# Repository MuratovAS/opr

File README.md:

# OPR
Open pocket router

## Screenshots

## In developing!!!

If you have questions, write suggestions in `Issues`

## Description
TODO:

## Specification

- CPU: MT7621A
- RAM: 2Gbit DDR3 
- USB: 3.0
- ETH: 3xGbE (RJ45)
- Display: SSD1306-0.91
- Flash: W25Q256FVEIG
- PowerBank: IP5328P
- Connectors: M.2 (2xPCIe+UART); mPCIe (1xPCIe+I2C+USB2+UART)
- PCB: 6 layers; JLC06161H-3313; Epoxy Filled & Capped; 0.15mm/0.3mm Via 

## Supported modules

- WIFI: MT7612E/MT7603E (x2 mPCIe)

## Changelog:

### v 0.1
- init

## Credit
```
https://github.com/kellertk/pwnagotchi-plugin-pisugar2
https://github.com/YC-Lammy/IP5328P-powerbank_design
https://github.com/zhaoxinyu0113/MT7621A_Router_HW_DIY'
https://github.com/cyijun/MT7621A-Router-Design
https://www.cnx-software.com/2015/05/14/firewrt-is-an-openwrt-802-11ac-board-powered-by-mediatek-mt7621a-processor/
https://bbs.t-firefly.com/forum.php?mod=viewthread&tid=543
http://en.techinfodepot.shoutwiki.com/wiki/Firefly_FireWRT
https://wikidevi.wi-cat.ru/MediaTek
https://whycan.com/t_2230.html
http://bbs.ntpcb.com/read-htm-tid-44619.html
https://www.elecfans.com/soft/21/2020/202003111179546.html
```

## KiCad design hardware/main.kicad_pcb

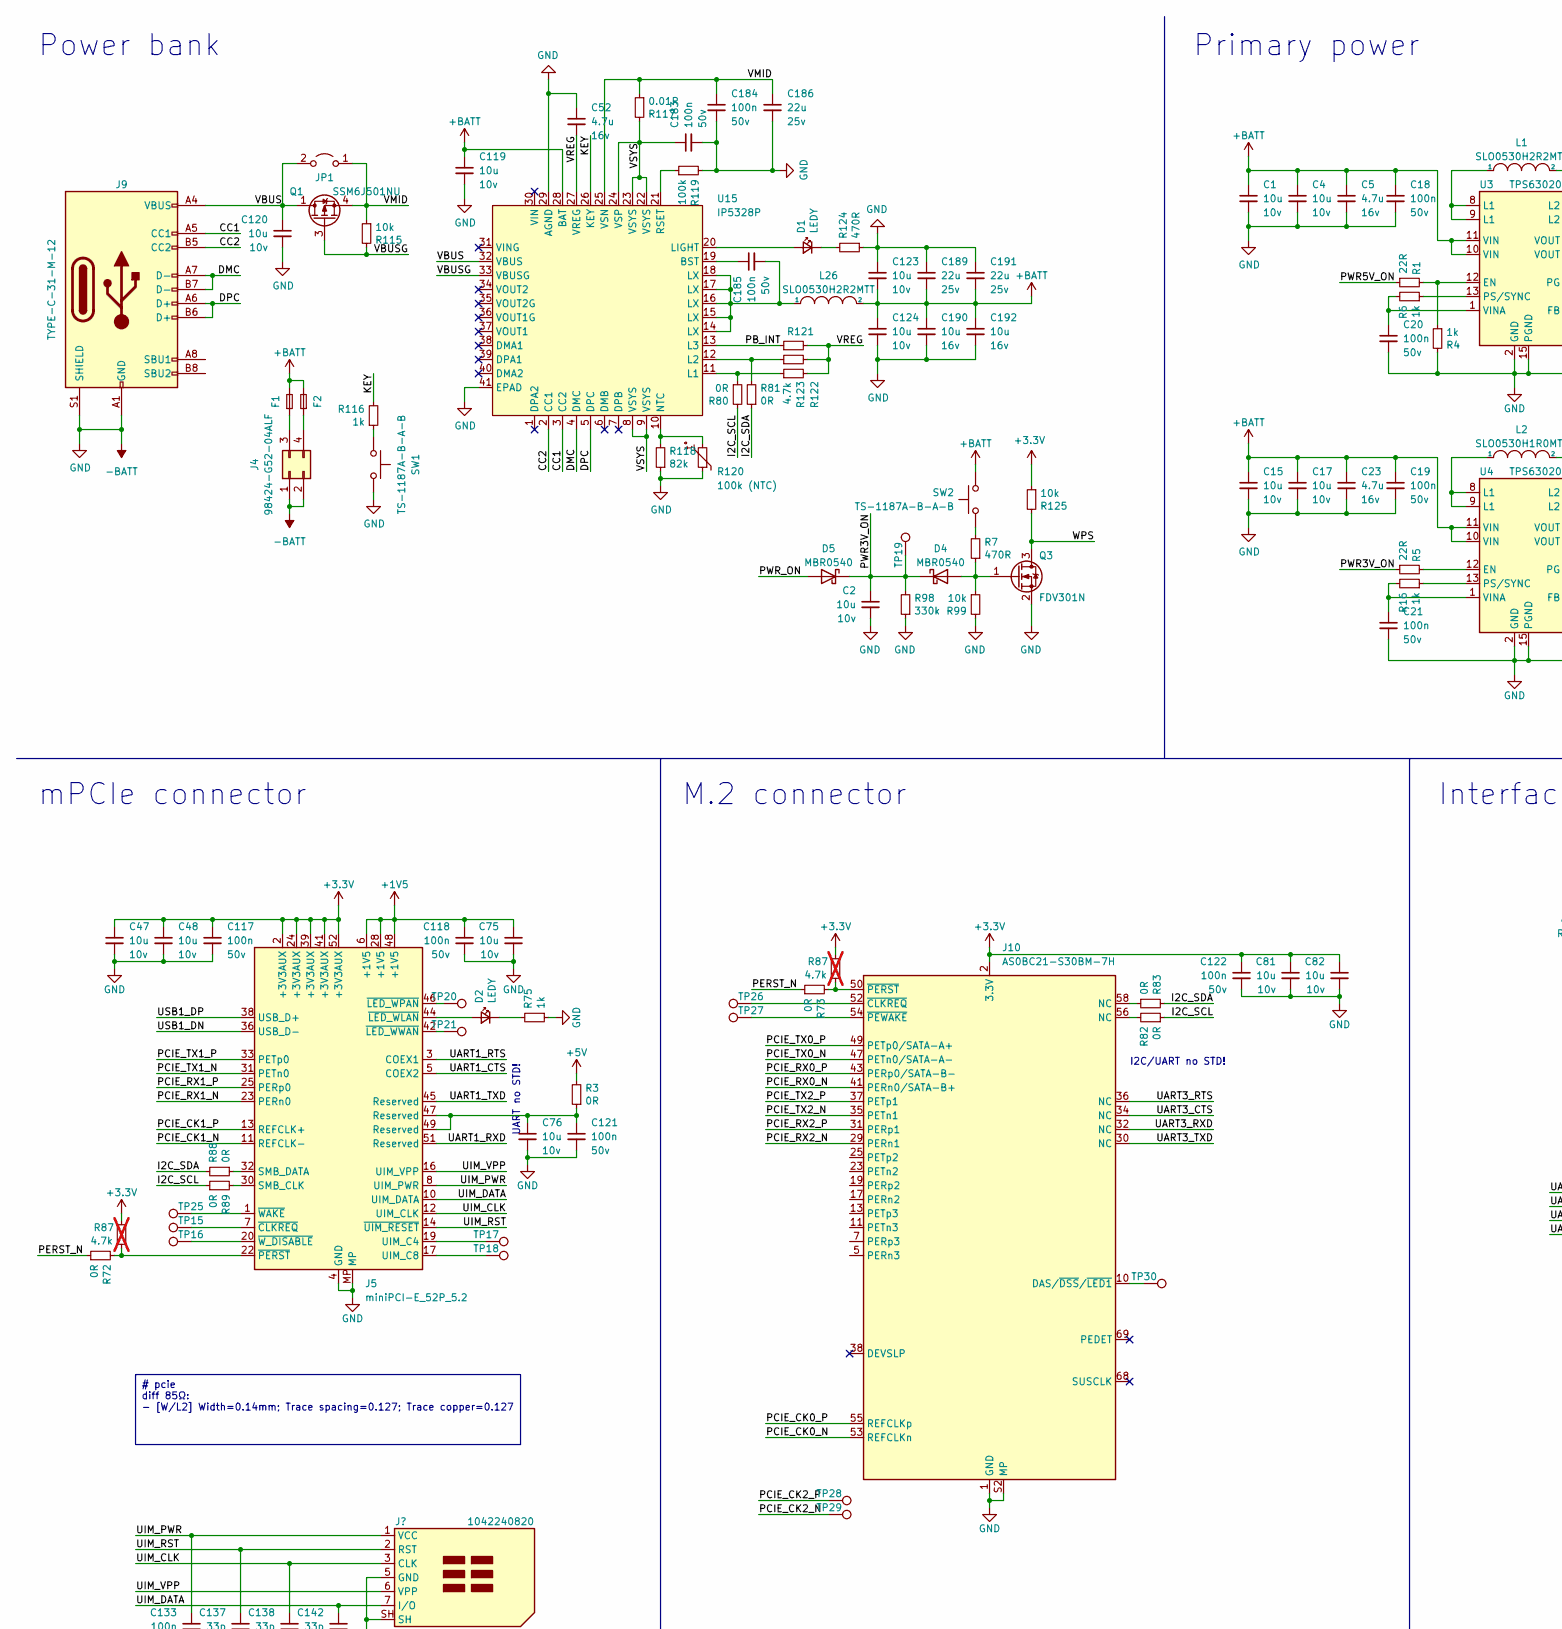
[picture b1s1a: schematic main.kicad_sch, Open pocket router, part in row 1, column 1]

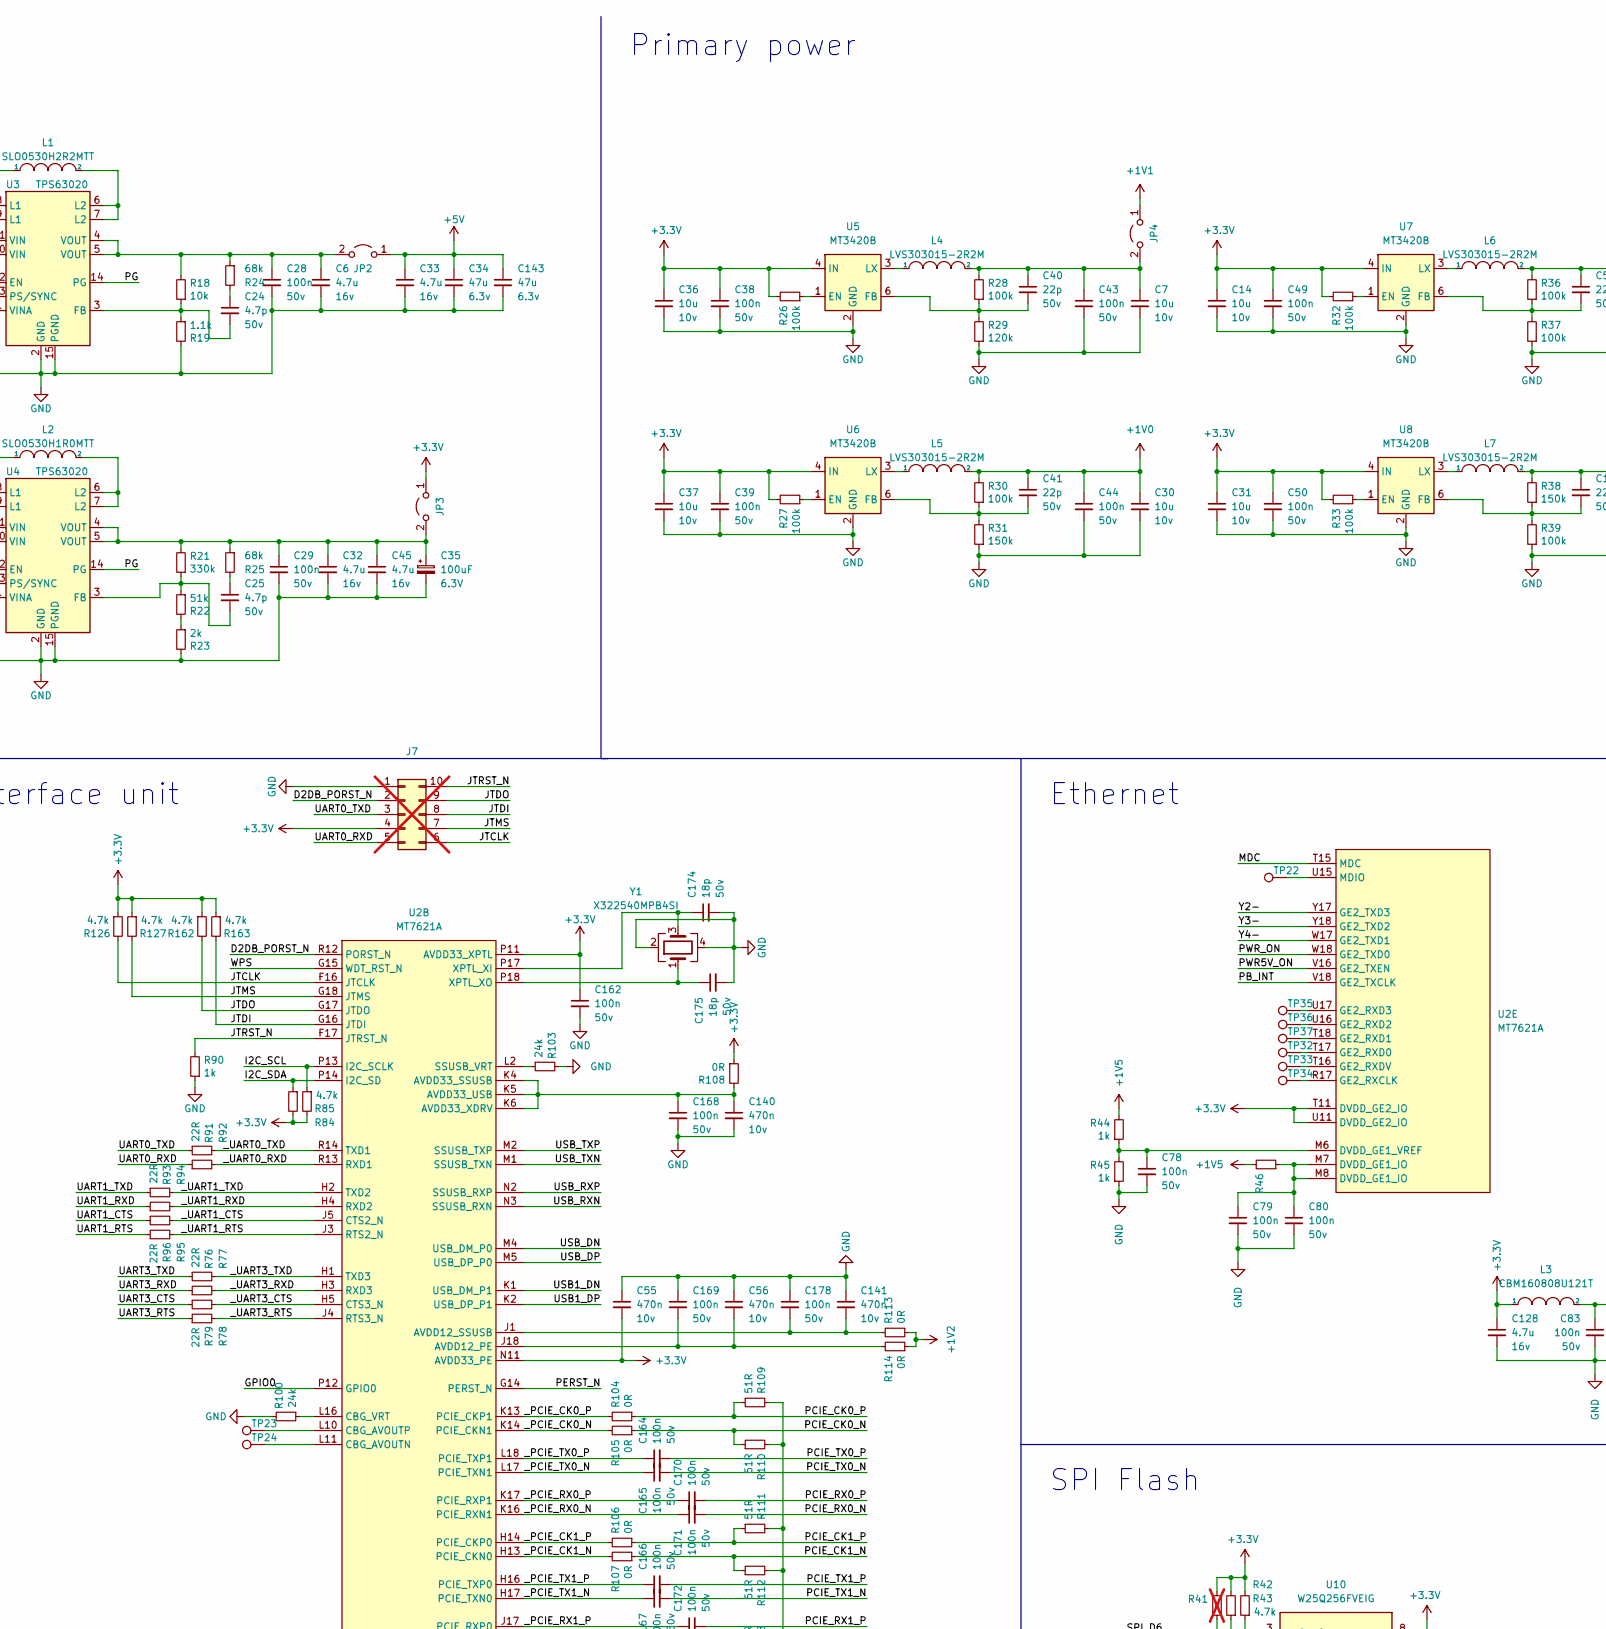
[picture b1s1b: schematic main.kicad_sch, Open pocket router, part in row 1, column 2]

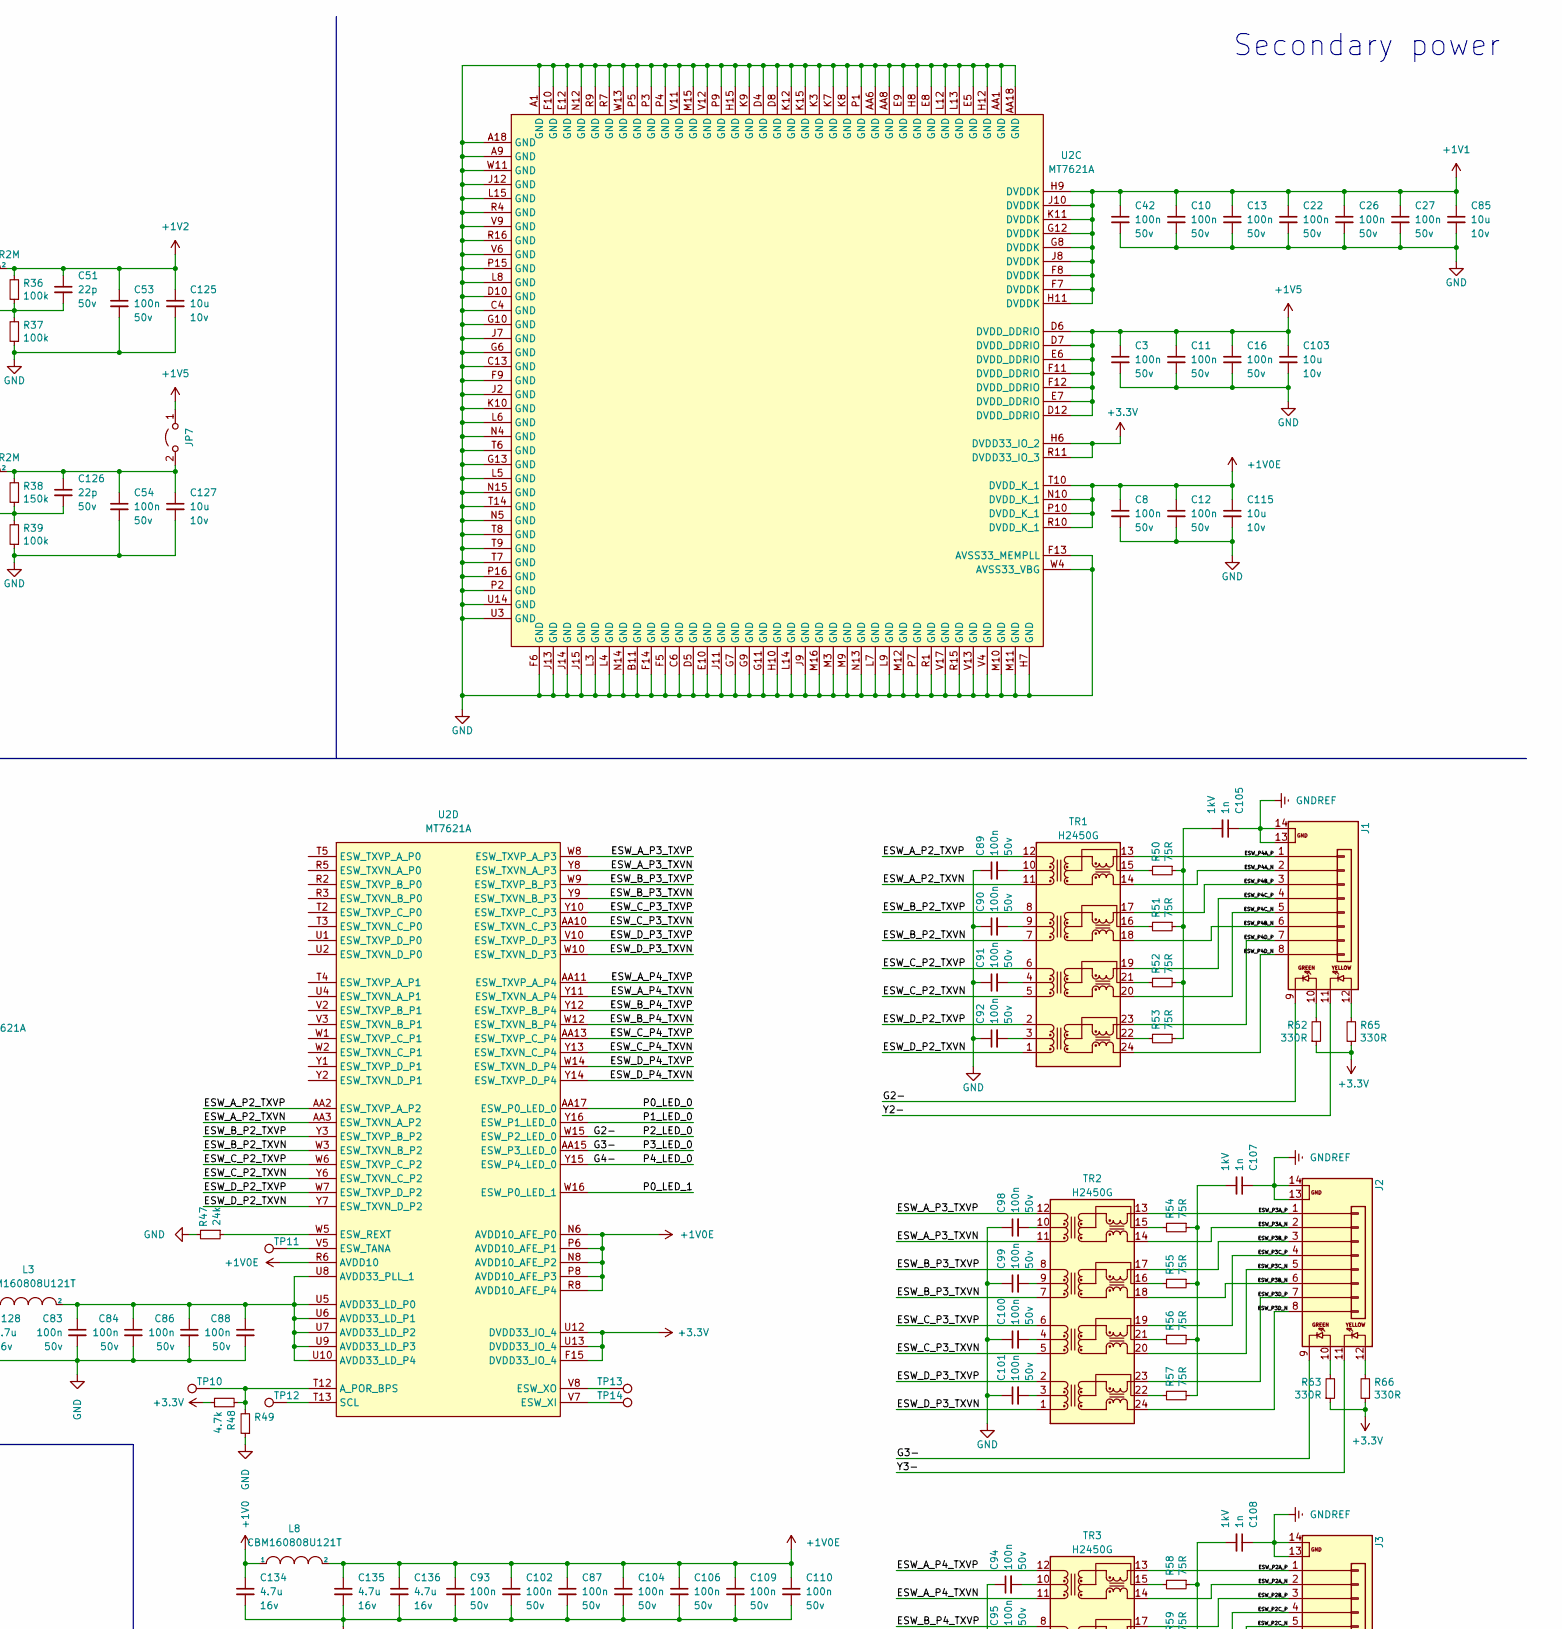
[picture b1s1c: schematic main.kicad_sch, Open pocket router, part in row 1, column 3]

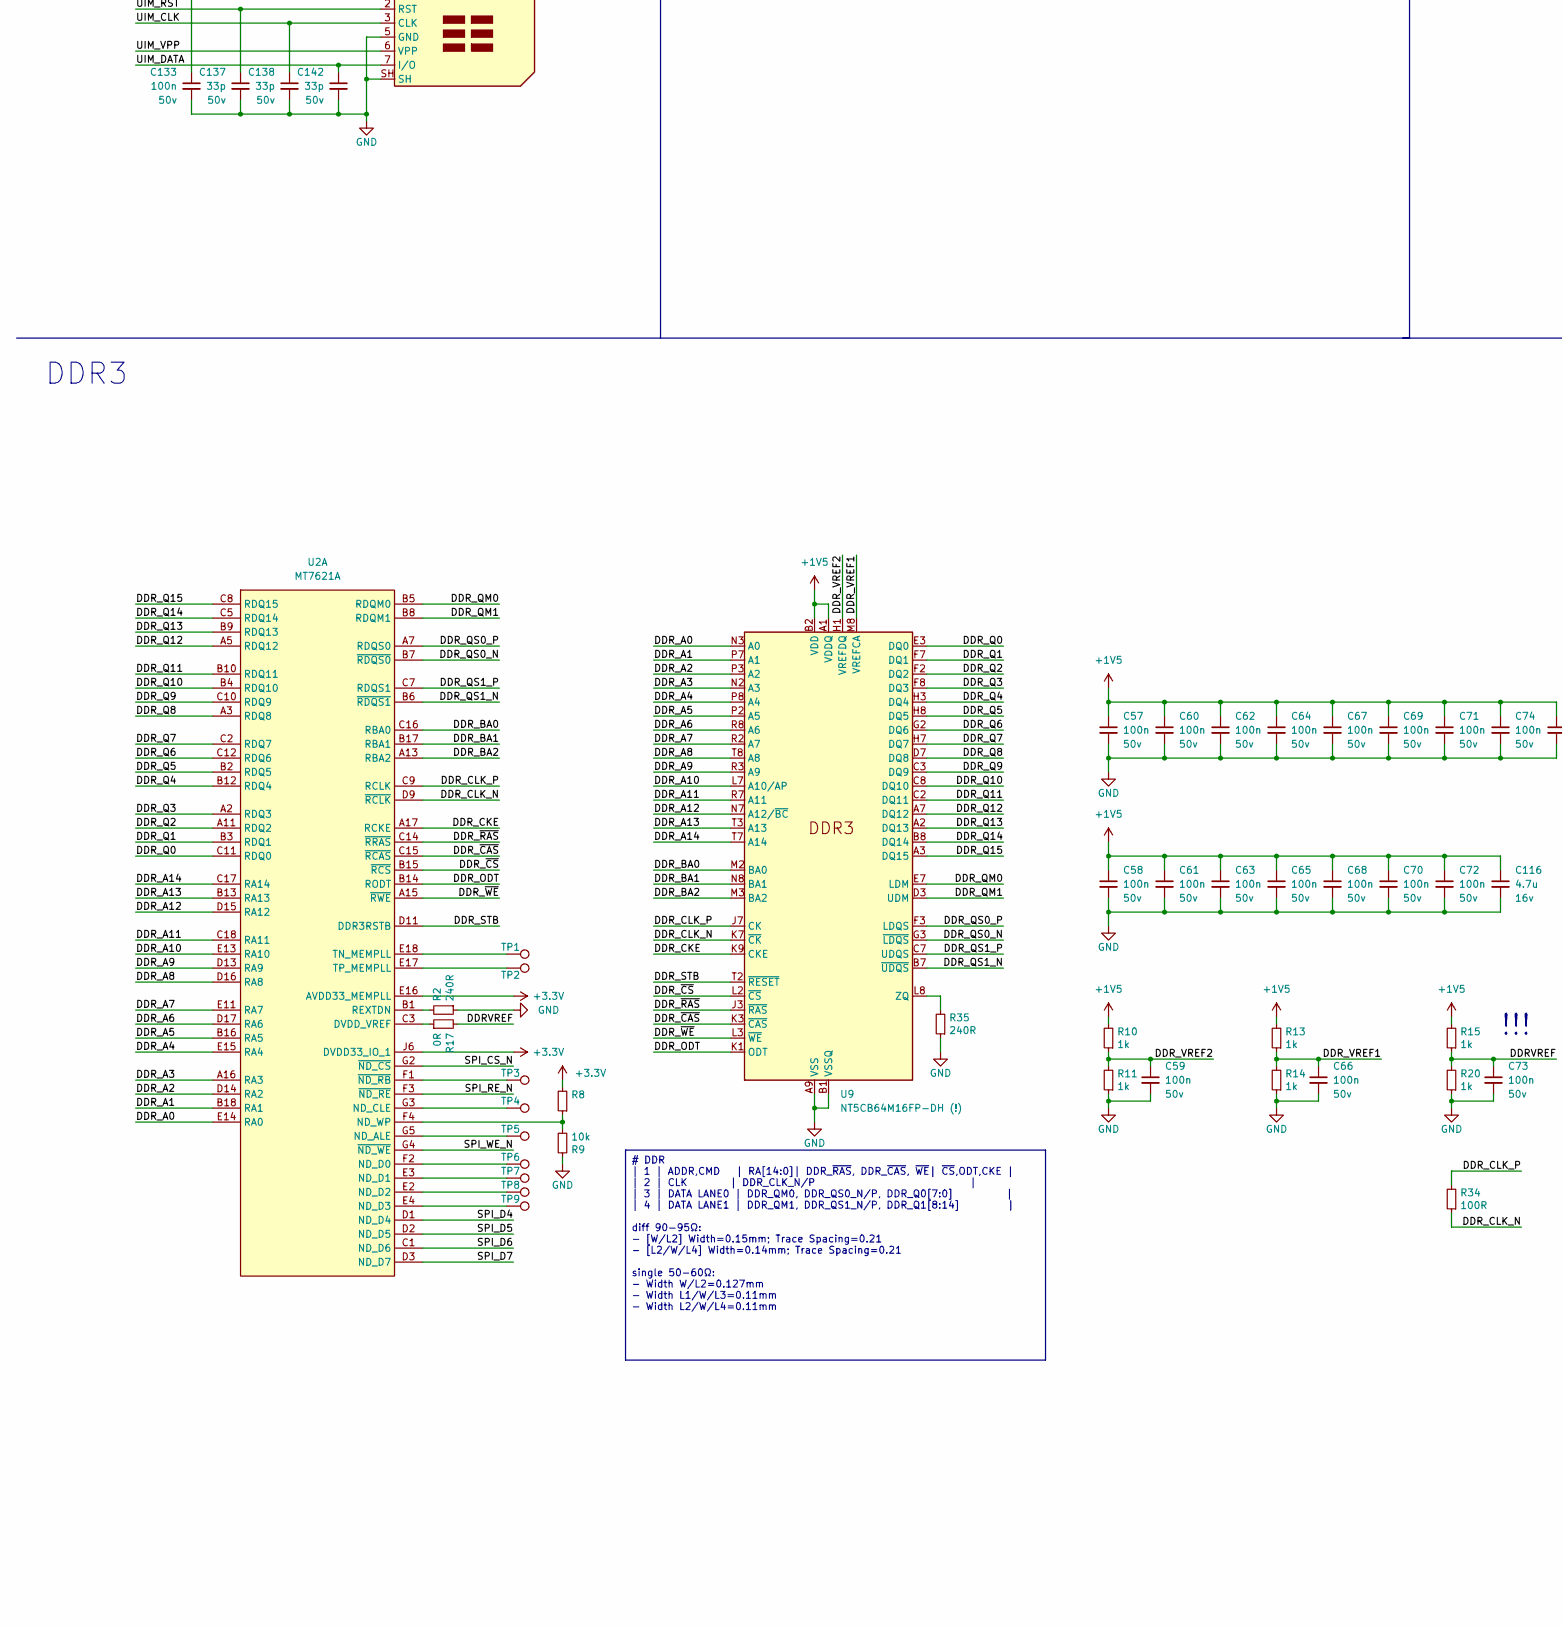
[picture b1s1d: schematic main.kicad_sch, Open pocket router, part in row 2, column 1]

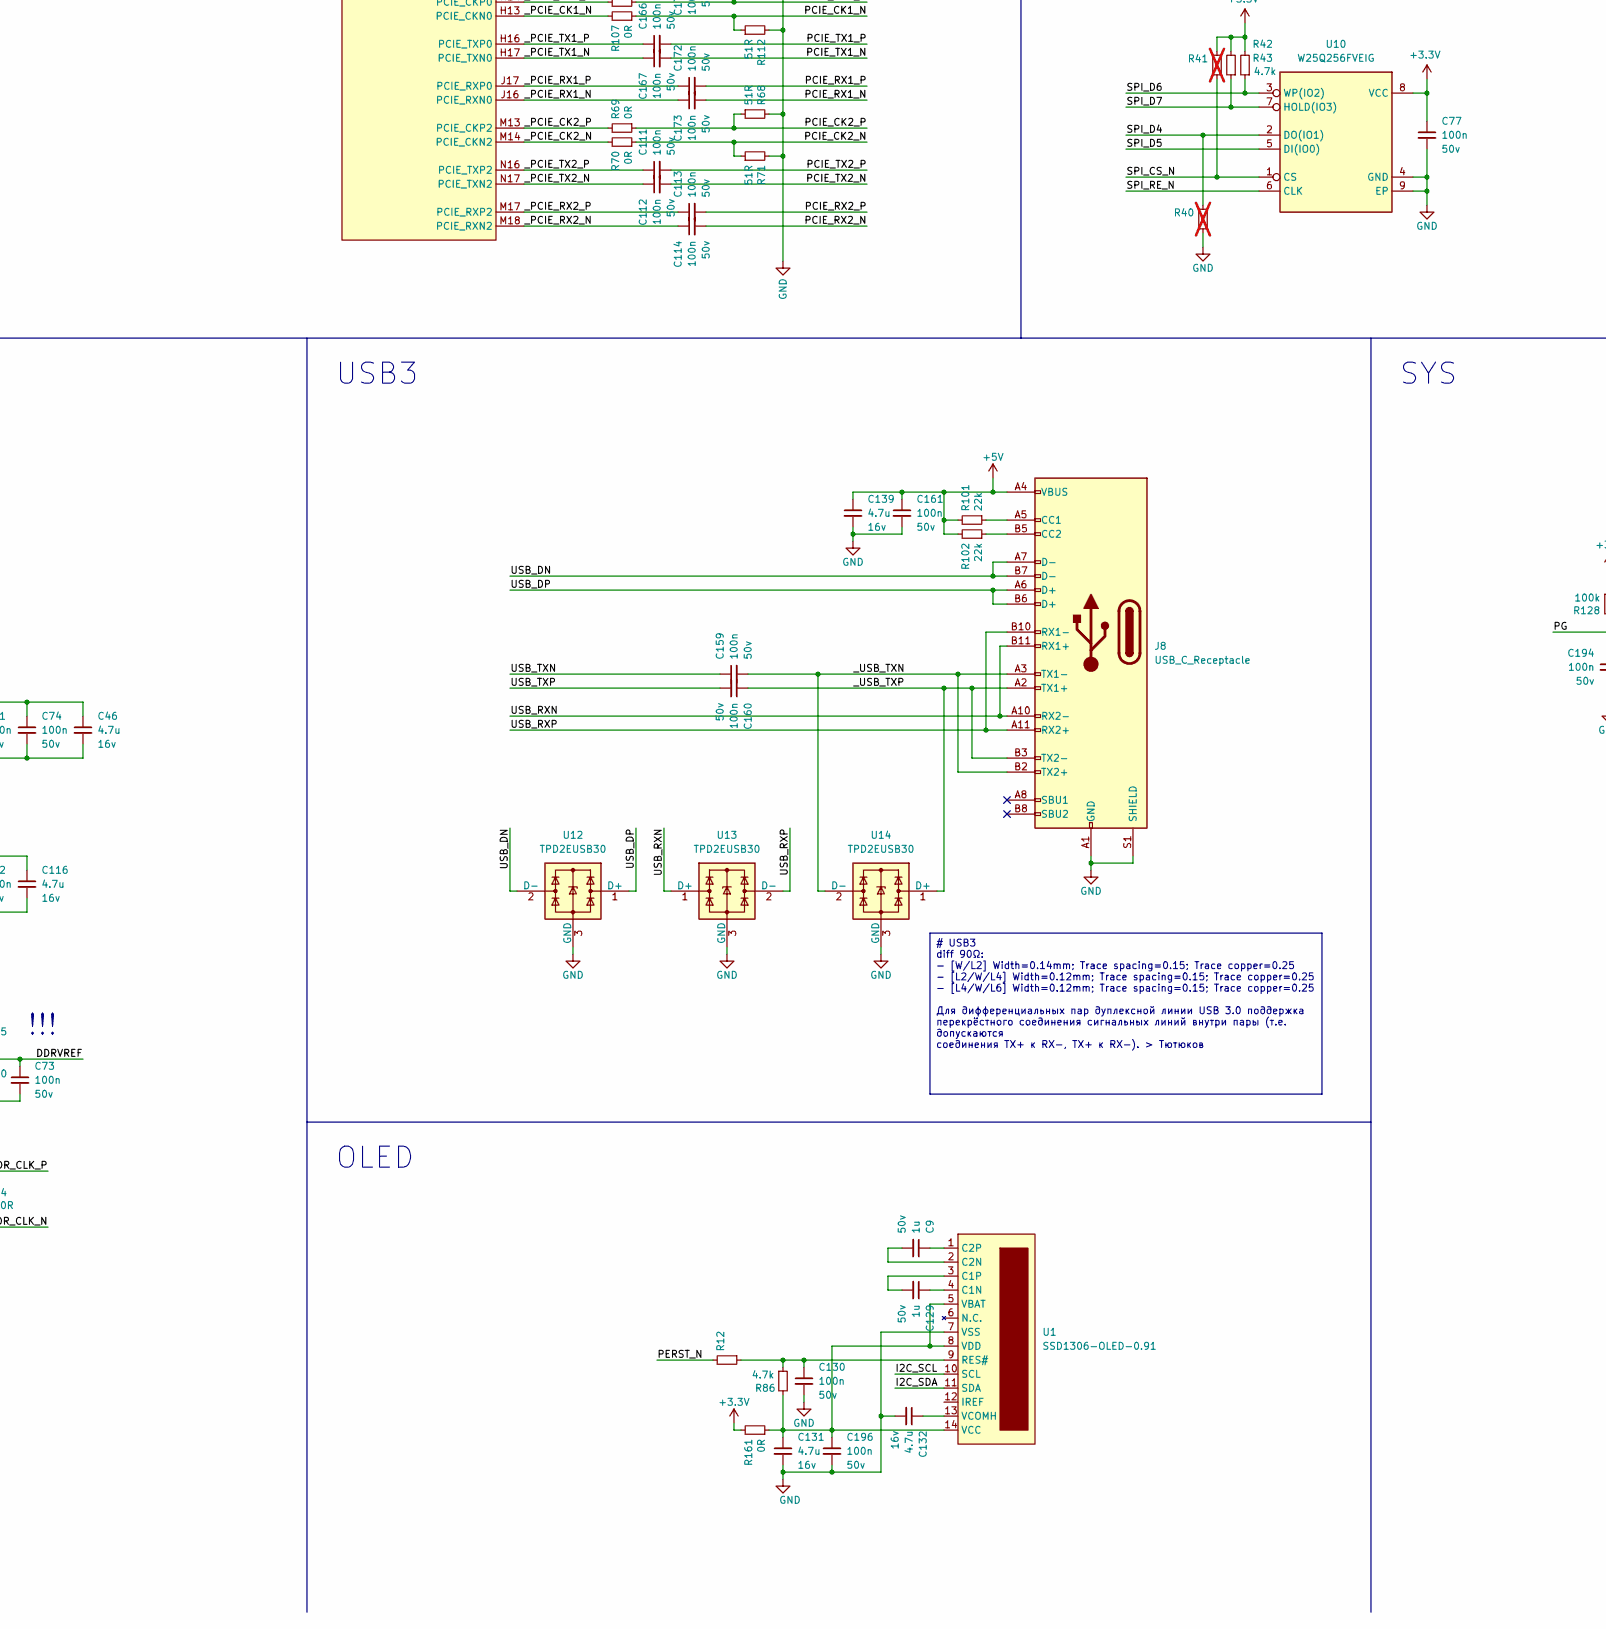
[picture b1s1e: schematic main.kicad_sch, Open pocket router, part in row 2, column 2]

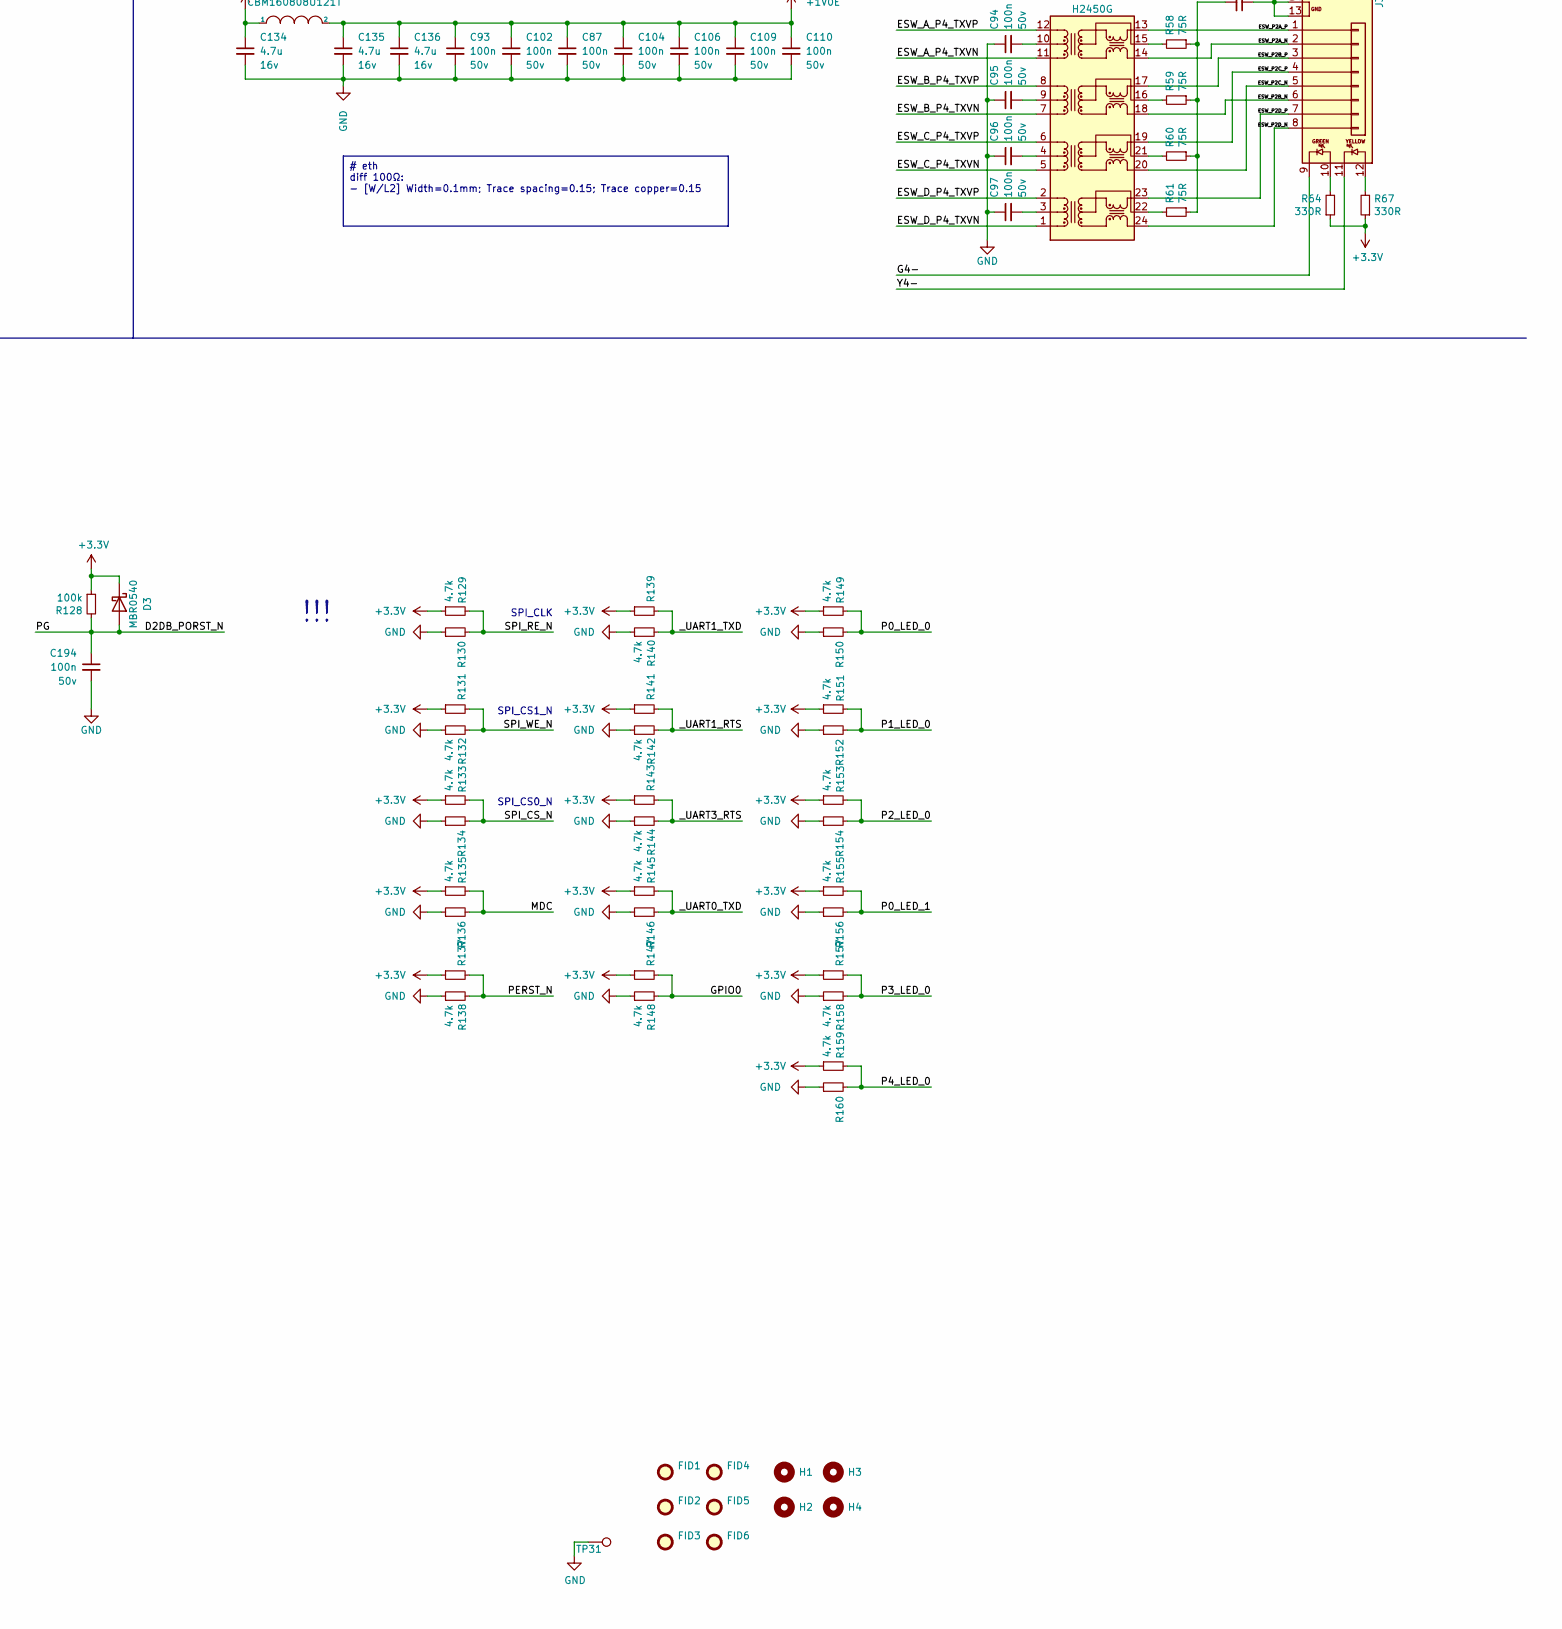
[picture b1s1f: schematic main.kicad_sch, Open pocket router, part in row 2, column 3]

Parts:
C1, C2, C4, C7, C14, C15, C17, C30, C31, C36, C37, C47, C48, C75, C76, C81, C82, C85, C103, C115, C119, C120, C123, C124, C125, C127: 10u; C_0603_1608Metric; Voltage 10v; lcsc C19702
C3, C8, C10, C11, C12, C13, C16, C18, C19, C20, C21, C22, C26, C27, C28, C29, C38, C39, C42, C43, C44, C49, C50, C53, C54, C57, C58, C59, C60, C61, C62, C63, C64, C65, C66, C67, C68, C69, C70, C71, C72, C73, C74, C77, C78, C79, C80, C83, C84, C86, C87, C88, C89, C90, C91, C92, C93, C94, C95, C96, C97, C98, C99, C100, C101, C102, C104, C106, C109, C110, C111, C112, C113, C114, C117, C118, C121, C122, C130, C133, C159, C160, C161, C162, C164, C165, C166, C167, C168, C169, C170, C171, C172, C173, C178, C183, C184, C185, C194, C196: 100n; C_0402_1005Metric; Voltage 50v; lcsc C307331
C5, C6, C23, C32, C33, C45, C46, C52, C116, C128, C131, C132, C134, C135, C136, C139: 4.7u; C_0603_1608Metric; Voltage 16v; lcsc C19666
C9, C129: 1u; C_0603_1608Metric; Voltage 50v; lcsc C15849
C24, C25: 4.7p; C_0402_1005Metric; Voltage 50v; lcsc C1569
C34, C143: 47u; C_0805_2012Metric; Voltage 6.3v; lcsc C16780
C35: 100uF; CP_EIA-3528-21_Kemet-B; Voltage 6.3V; lcsc C16133
C40, C41, C51, C126: 22p; C_0402_1005Metric; Voltage 50v; lcsc C1555
C55, C56, C140, C141: 470n; C_0402_1005Metric; Voltage 10v; lcsc C47339
C105, C107, C108: 1n; C_0805_2012Metric; Voltage 1kV; lcsc C303890
C137, C138, C142: 33p; C_0402_1005Metric; Voltage 50v; lcsc C1562
C174, C175: 18p; C_0402_1005Metric; Voltage 50v; lcsc C1549
C186, C189, C191: 22u; C_0805_2012Metric; Voltage 25v; lcsc C45783
C190, C192: 10u; C_0805_2012Metric; Voltage 16v; lcsc C95841
D1, D2: LEDY; D_0603_1608Metric; lcsc C72038
D3, D4, D5: MBR0540; D_SOD-123
F1, F2: 12T.30000063AG12S1B02; Fuse_1206_3216Metric; lcsc C140478
FID1, FID2, FID3, FID4, FID5, FID6: F; Fiducial_1mm_Mask3mm
H1, H2, H3, H4: H; MountingHole_3.2mm_M3_DIN965_Pad
J1, J2, J3: DS1128-09-S8B8X; RJ45_DS1128-09-S8B8X; lcsc C86578
J4: 98424-G52-04ALF; PinSocket_2x02_P2.00mm_Vertical_SMD; lcsc C216040
J5: miniPCI-E_52P_5.2; BUS_PCI_Express_Mini_Dual; lcsc C16250
J7: PinHeader_2x05_P1.27mm_Vertical; not fitted
J8: USB_C_Receptacle; HRS_CX90B1-24P; lcsc C2681555
J9: TYPE-C-31-M-12; USB_C_Receptacle_HRO_TYPE-C-31-M-12; lcsc C165948
J10: AS0BC21-S30BM-7H; Bus_M.2_Socket_M; lcsc C2832351
JP1, JP2, JP3, JP4, JP7: JP; SolderJumper_Open_Pad0.5x0.8mm
L1, L26: SLO0530H2R2MTT; Power_inductor_SMD_0530; lcsc C325962
L2: SLO0530H1R0MTT; Power_inductor_SMD_0530; lcsc C325960
L3, L8: CBM160808U121T; L_0603_1608Metric; lcsc C62708
L4, L5, L6, L7: LVS303015-2R2M; L_Wuerth_MAPI-3015; lcsc C285837
Q1: SSM6J501NU; U-MOSVI; lcsc C146326
Q3: FDV301N; SOT-23; lcsc C15310
R1, R5, R76, R77, R78, R79, R91, R92, R93, R94, R95, R96: 22R; R_0402_1005Metric; lcsc C25092
R2, R35: 240R; R_0402_1005Metric; lcsc C114755
R3, R17, R69, R70, R72, R73, R80, R81, R82, R83, R88, R89, R104, R105, R106, R107, R108, R113, R114, R161: 0R; R_0402_1005Metric; lcsc C17168
R4, R6, R10, R11, R13, R14, R15, R16, R20, R44, R45, R75, R90, R116: 1k; R_0402_1005Metric; lcsc C11702
R7, R124: 470R; R_0402_1005Metric; lcsc C25117
R8, R12, R46, R49, R121, R130, R131, R134, R136, R137, R139, R141, R143, R146, R147, R150, R152, R154, R156, R157, R160: R_0402_1005Metric
R9, R18, R99, R115, R125: 10k; R_0402_1005Metric; lcsc C25744
R19: 1.1k; R_0402_1005Metric; lcsc C325543
R21, R98: 330k; R_0402_1005Metric; lcsc C25778
R22: 51k; R_0402_1005Metric; lcsc C25794
R23: 2k; R_0402_1005Metric; lcsc C100608
R24, R25: 68k; R_0402_1005Metric; lcsc C36871
R26, R27, R28, R30, R32, R33, R36, R37, R39, R119, R128: 100k; R_0402_1005Metric; lcsc C25741
R29: 120k; R_0402_1005Metric; lcsc C25750
R31, R38: 150k; R_0402_1005Metric; lcsc C25755
R34: 100R; R_0402_1005Metric; lcsc C153111
R40, R41: R_0402_1005Metric; not fitted
R42, R43, R48, R84, R85, R86, R122, R123, R126, R127, R129, R132, R133, R135, R138, R140, R142, R144, R145, R148, R149, R151, R153, R155, R158, R159, R162, R163: 4.7k; R_0402_1005Metric; lcsc C25900
R47, R100, R103: 24k; R_0402_1005Metric; lcsc C25769
R50, R51, R52, R53, R54, R55, R56, R57, R58, R59, R60, R61: 75R; R_0402_1005Metric; lcsc C25133
R62, R63, R64, R65, R66, R67: 330R; R_0402_1005Metric; lcsc C25104
R68, R71, R109, R110, R111, R112: 51R; R_0402_1005Metric; lcsc C25125
R87: 4.7k; R_0402_1005Metric; lcsc C25900; not fitted
R101, R102: 22k; R_0402_1005Metric; lcsc C25768
R117: 0.01R; R_1206_3216Metric; lcsc C778444
R118: 82k; R_0402_1005Metric; lcsc C137932
R120: 100k (NTC); R_0805_2012Metric; lcsc C95970
SW1, SW2: TS-1187A-B-A-B; SW_SPST_TL3342; lcsc C318884
TP1, TP2, TP3, TP4, TP5, TP6, TP7, TP8, TP9, TP10, TP11, TP12, TP13, TP14, TP15, TP16, TP17, TP18, TP19, TP20, TP21, TP22, TP23, TP24, TP25, TP26, TP27, TP28, TP29, TP30, TP31, TP32, TP33, TP34, TP35, TP36, TP37: TP; TestPoint_Pad_D1mm
TR1, TR2, TR3: H2450G; Transformer_Ethernet_E-NETTR_24; lcsc C4155005
U1: SSD1306-OLED-0.91; SSD1306-oled-0.91
U2: MT7621A; TFBGA-387_11.7x13.6mm_P0.65mm
U3, U4: TPS63020; DFN-14-1EP_3x4mm_P0.5mm_EP1.7x3.3mm; lcsc C15483
U5, U6, U7, U8: MT3420B; SOT-23-6; lcsc C88169
U9: NT5CB64M16FP-DH (!); BGA-96_9.0x13.0mm_Layout2x3x16_P0.8mm; lcsc C2909894
U10: W25Q256FVEIG; WSON-8-1EP_8x6mm_P1.27mm_EP3.4x4mm; lcsc C2803442
U12, U13, U14: TPD2EUSB30; Texas_DRT-3; lcsc C2844720
U15: IP5328P; QFN-40-1EP_6x6mm_P0.5mm_EP4.6x4.6mm
Y1: X322540MPB4SI; Oscillator_SMD_SMD3225-4P; lcsc C9010

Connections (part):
+1V0: C30.1, C41.1, C44.1, C134.1, L5.2, L8.1, R30.2
+1V0E: C8.1, C12.1, C87.1, C93.1, C102.1, C104.1, C106.1, C109.1, C110.1, C115.1, C135.1, C136.1, L8.2, U2.N6 (AVDD10_AFE_P0), U2.N8 (AVDD10_AFE_P2), U2.N10 (DVDD_K_1), U2.P6 (AVDD10_AFE_P1), U2.P8 (AVDD10_AFE_P3), U2.P10 (DVDD_K_1), U2.R6 (AVDD10), U2.R8 (AVDD10_AFE_P4), U2.R10 (DVDD_K_1), U2.T10 (DVDD_K_1)
+1V1: C10.1, C13.1, C22.1, C26.1, C27.1, C42.1, C85.1, JP4.1 (A), U2.F7 (DVDDK), U2.F8 (DVDDK), U2.G8 (DVDDK), U2.G12 (DVDDK), U2.H9 (DVDDK), U2.H11 (DVDDK), U2.J8 (DVDDK), U2.J10 (DVDDK), U2.K11 (DVDDK)
+1V2: C51.1, C53.1, C125.1, L6.2, R36.2, R113.1, R114.1
+1V5: C3.1, C11.1, C16.1, C46.1, C57.1, C58.1, C60.1, C61.1, C62.1, C63.1, C64.1, C65.1, C67.1, C68.1, C69.1, C70.1, C71.1, C72.1, C74.1, C75.1, C103.1, C116.1, C118.1, J5.6 (+1V5), J5.28 (+1V5), J5.48 (+1V5), JP7.1 (A), R10.2, R13.2, R15.2, R44.2, R46.2, U2.D6 (DVDD_DDRIO), U2.D7 (DVDD_DDRIO), U2.D12 (DVDD_DDRIO), U2.E6 (DVDD_DDRIO), U2.E7 (DVDD_DDRIO), U2.F11 (DVDD_DDRIO), U2.F12 (DVDD_DDRIO), U9.A1 (VDDQ), U9.A8 (VDDQ), U9.B2 (VDD), U9.C1 (VDDQ), U9.C9 (VDDQ), U9.D2 (VDDQ), U9.D9 (VDD), U9.E9 (VDDQ), U9.F1 (VDDQ), U9.G7 (VDD), U9.H2 (VDDQ), U9.H9 (VDDQ), U9.K2 (VDD), U9.K8 (VDD), U9.N1 (VDD), U9.N9 (VDD), U9.R1 (VDD), U9.R9 (VDD)
+3V3: C14.1, C31.1, C36.1, C37.1, C38.1, C39.1, C47.1, C48.1, C49.1, C50.1, C55.2, C77.1, C81.1, C82.1, C117.1, C122.1, C128.1, C162.1, D3.1 (K), J5.2 (+3V3AUX), J5.24 (+3V3AUX), J5.39 (+3V3AUX), J5.41 (+3V3AUX), J5.52 (+3V3AUX), J7.4, J10.2 (3.3V), J10.4 (3.3V), J10.12 (3.3V), J10.14 (3.3V), J10.16 (3.3V), J10.18 (3.3V), J10.70 (3.3V), J10.72 (3.3V), J10.74 (3.3V), JP3.1 (A), L3.1, R8.2, R26.2, R27.2, R32.2, R33.2, R41.2, R42.2, R43.2, R48.1, R62.1, R63.1, R64.1, R65.1, R66.1, R67.1, R84.2, R85.2, R87.2, R108.1, R125.1, R126.1, R127.1, R128.1, R129.1, R131.1, R133.1, R135.1, R137.1, R139.1, R141.1, R143.1, R145.1, R147.1, R149.1, R151.1, R153.1, R155.1, R157.1, R159.1, R161.2, R162.1, R163.1, U2.E16 (AVDD33_MEMPLL), U2.F15 (DVDD33_IO_4)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; also elsewhere on the board
+5V: C33.1, C34.1, C139.1, C143.1, C161.1, J8.A4 (VBUS), J8.A9 (VBUS), J8.B4 (VBUS), J8.B9 (VBUS), JP2.1 (A), R3.2, R101.2, R102.2
+BATT: C1.1, C4.1, C5.1, C15.1, C17.1, C18.1, C19.1, C23.1, C119.1, C123.2, C124.1, C189.2, C190.1, C191.2, C192.1, F1.2, F2.2, L26.2, SW2.2, U3.10 (VIN), U3.11 (VIN), U4.10 (VIN), U4.11 (VIN), U15.28 (BAT)
/CC1: J9.A5 (CC1), U15.3 (CC2)
/CC2: J9.B5 (CC2), U15.2 (CC1)
/D2DB_PORST_N: C194.1, D3.2 (A), J7.2, R128.2, U2.R12 (PORST_N), U3.14 (PG), U4.14 (PG)
/DDRVREF: C73.1, R15.1, R17.2, R20.2
/DDR_A0: U2.E14 (RA0), U9.N3 (A0)
/DDR_A1: U2.B18 (RA1), U9.P7 (A1)
/DDR_A2: U2.D14 (RA2), U9.P3 (A2)
/DDR_A3: U2.A16 (RA3), U9.N2 (A3)
/DDR_A4: U2.E15 (RA4), U9.P8 (A4)
/DDR_A5: U2.B16 (RA5), U9.P2 (A5)
/DDR_A6: U2.D17 (RA6), U9.R8 (A6)
/DDR_A7: U2.E11 (RA7), U9.R2 (A7)
/DDR_A8: U2.D16 (RA8), U9.T8 (A8)
/DDR_A9: U2.D13 (RA9), U9.R3 (A9)
/DDR_A10: U2.E13 (RA10), U9.L7 (A10/AP)
/DDR_A11: U2.C18 (RA11), U9.R7 (A11)
/DDR_A12: U2.D15 (RA12), U9.N7 (A12/~BC)
/DDR_A13: U2.B13 (RA13), U9.T3 (A13)
/DDR_A14: U2.C17 (RA14), U9.T7 (A14)
/DDR_BA0: U2.C16 (RBA0), U9.M2 (BA0)
/DDR_BA1: U2.B17 (RBA1), U9.N8 (BA1)
/DDR_BA2: U2.A13 (RBA2), U9.M3 (BA2)
/DDR_CKE: U2.A17 (RCKE), U9.K9 (CKE)
/DDR_CLK_N: R34.1, U2.D9 (~RCLK), U9.K7 (~CK)
/DDR_CLK_P: R34.2, U2.C9 (RCLK), U9.J7 (CK)
/DDR_ODT: U2.B14 (RODT), U9.K1 (ODT)
/DDR_Q0: U2.C11 (RDQ0), U9.E3 (DQ0)
/DDR_Q1: U2.B3 (RDQ1), U9.F7 (DQ1)
/DDR_Q2: U2.A11 (RDQ2), U9.F2 (DQ2)
/DDR_Q3: U2.A2 (RDQ3), U9.F8 (DQ3)
/DDR_Q4: U2.B12 (RDQ4), U9.H3 (DQ4)
/DDR_Q5: U2.B2 (RDQ5), U9.H8 (DQ5)
/DDR_Q6: U2.C12 (RDQ6), U9.G2 (DQ6)
/DDR_Q7: U2.C2 (RDQ7), U9.H7 (DQ7)
/DDR_Q8: U2.A3 (RDQ8), U9.D7 (DQ8)
/DDR_Q9: U2.C10 (RDQ9), U9.C3 (DQ9)
/DDR_Q10: U2.B4 (RDQ10), U9.C8 (DQ10)
/DDR_Q11: U2.B10 (RDQ11), U9.C2 (DQ11)
/DDR_Q12: U2.A5 (RDQ12), U9.A7 (DQ12)
/DDR_Q13: U2.B9 (RDQ13), U9.A2 (DQ13)
/DDR_Q14: U2.C5 (RDQ14), U9.B8 (DQ14)
/DDR_Q15: U2.C8 (RDQ15), U9.A3 (DQ15)
/DDR_QM0: U2.B5 (RDQM0), U9.E7 (LDM)
/DDR_QM1: U2.B8 (RDQM1), U9.D3 (UDM)
/DDR_QS0_N: U2.B7 (~RDQS0), U9.G3 (~LDQS)
/DDR_QS0_P: U2.A7 (RDQS0), U9.F3 (LDQS)
/DDR_QS1_N: U2.B6 (~RDQS1), U9.B7 (~UDQS)
/DDR_QS1_P: U2.C7 (RDQS1), U9.C7 (UDQS)
/DDR_STB: U2.D11 (DDR3RSTB), U9.T2 (~RESET)
/DDR_VREF1: C66.1, R13.1, R14.2, U9.M8 (VREFCA)
/DDR_VREF2: C59.1, R10.1, R11.2, U9.H1 (VREFDQ)
/DDR_~CAS: U2.C15 (~RCAS), U9.K3 (~CAS)
/DDR_~CS: U2.B15 (~RCS), U9.L2 (~CS)
/DDR_~RAS: U2.C14 (~RRAS), U9.J3 (~RAS)
/DDR_~WE: U2.A15 (~RWE), U9.L3 (~WE)
/DMC: J9.A7 (D-), J9.B7 (D-), U15.4 (DMC)
/DPC: J9.A6 (D+), J9.B6 (D+), U15.5 (DPC)
/ESW_A_P2_TXVN: TR1.11 (TD4+), U2.AA3 (ESW_TXVN_A_P2)
/ESW_A_P2_TXVP: TR1.12 (TD4-), U2.AA2 (ESW_TXVP_A_P2)
/ESW_A_P3_TXVN: TR2.11 (TD4+), U2.Y8 (ESW_TXVN_A_P3)
/ESW_A_P3_TXVP: TR2.12 (TD4-), U2.W8 (ESW_TXVP_A_P3)
/ESW_A_P4_TXVN: TR3.11 (TD4+), U2.Y11 (ESW_TXVN_A_P4)
/ESW_A_P4_TXVP: TR3.12 (TD4-), U2.AA11 (ESW_TXVP_A_P4)
/ESW_B_P2_TXVN: TR1.7 (CT), U2.W3 (ESW_TXVN_B_P2)
/ESW_B_P2_TXVP: TR1.8 (TD3+), U2.Y3 (ESW_TXVP_B_P2)
/ESW_B_P3_TXVN: TR2.7 (CT), U2.Y9 (ESW_TXVN_B_P3)
/ESW_B_P3_TXVP: TR2.8 (TD3+), U2.W9 (ESW_TXVP_B_P3)
/ESW_B_P4_TXVN: TR3.7 (CT), U2.W12 (ESW_TXVN_B_P4)
/ESW_B_P4_TXVP: TR3.8 (TD3+), U2.Y12 (ESW_TXVP_B_P4)
/ESW_C_P2_TXVN: TR1.5 (TD2+), U2.Y6 (ESW_TXVN_C_P2)
/ESW_C_P2_TXVP: TR1.6 (TD2-), U2.W6 (ESW_TXVP_C_P2)
/ESW_C_P3_TXVN: TR2.5 (TD2+), U2.AA10 (ESW_TXVN_C_P3)
/ESW_C_P3_TXVP: TR2.6 (TD2-), U2.Y10 (ESW_TXVP_C_P3)
/ESW_C_P4_TXVN: TR3.5 (TD2+), U2.Y13 (ESW_TXVN_C_P4)
/ESW_C_P4_TXVP: TR3.6 (TD2-), U2.AA13 (ESW_TXVP_C_P4)
/ESW_D_P2_TXVN: TR1.1 (CT), U2.Y7 (ESW_TXVN_D_P2)
/ESW_D_P2_TXVP: TR1.2 (TD1+), U2.W7 (ESW_TXVP_D_P2)
/ESW_D_P3_TXVN: TR2.1 (CT), U2.W10 (ESW_TXVN_D_P3)
/ESW_D_P3_TXVP: TR2.2 (TD1+), U2.V10 (ESW_TXVP_D_P3)
/ESW_D_P4_TXVN: TR3.1 (CT), U2.Y14 (ESW_TXVP_D_P4)
/ESW_D_P4_TXVP: TR3.2 (TD1+), U2.W14 (ESW_TXVN_D_P4)
/ESW_P2C_P: J3.4, TR3.19 (MX2-)
/ESW_P2D_N: J3.8, TR3.24 (CT)
/ESW_P3A_N: J2.2, TR2.14 (MX4+)
/ESW_P3A_P: J2.1, TR2.13 (MX4-)
/ESW_P3B_N: J2.6, TR2.18 (CT)
/ESW_P3B_P: J2.3, TR2.17 (MX3+)
/ESW_P3C_N: J2.5, TR2.20 (MX2+)
/ESW_P3C_P: J2.4, TR2.19 (MX2-)
/ESW_P3D_N: J2.8, TR2.24 (CT)
/ESW_P3D_P: J2.7, TR2.23 (MX1+)
/ESW_P4A_N: J1.2, TR1.14 (MX4+)
/ESW_P4A_P: J1.1, TR1.13 (MX4-)
/ESW_P4B_N: J1.6, TR1.18 (CT)
/ESW_P4B_P: J1.3, TR1.17 (MX3+)
/ESW_P4C_N: J1.5, TR1.20 (MX2+)
/ESW_P4C_P: J1.4, TR1.19 (MX2-)
/ESW_P4D_N: J1.8, TR1.24 (CT)
/ESW_P4D_P: J1.7, TR1.23 (MX1+)
/G2-: J1.9, R153.2, R154.2, U2.W15 (ESW_P2_LED_0)
/G3-: J2.9, R157.2, R158.2, U2.AA15 (ESW_P3_LED_0)
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
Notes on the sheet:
# eth diff 100Ω: - [W/L2] Width=0.1mm; Trace spacing=0.15; Trace copper=0.15
# USB3 diff 90Ω: - [W/L2] Width=0.14mm; Trace spacing=0.15; Trace copper=0.25 - [L2/W/L4] Width=0.12mm; Trace spacing=0.15; Trace copper=0.25 - [L4/W/L6] Width=0.12mm; Trace spacing=0.15; Trace copper=0.25 Для дифференциальных пар дуплексной линии USB 3.0 поддержка перекрёстного соединения сигнальн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
# DDR | 1 | ADDR,CMD | RA[14:0]| DDR_~{RAS}, DDR_~{CAS}, ~{WE}| ~{CS},ODT,CKE | | 2 | CLK | DDR_CLK_N/P | | 3 | DATA LANE0 | DDR_QM0, DDR_QS0_N/P, DDR_Q0[7:0] | | 4 | DATA LANE1 | DDR_QM1, DDR_QS1_N/P, DDR_Q1[8:14] | diff 90-95Ω: - [W/L2] Width=0.15mm; Trace Spacing=0.21 - [L2/W/L4] Width=0.14mm; T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
# pcie diff 85Ω: - [W/L2] Width=0.14mm; Trace spacing=0.127; Trace copper=0.127
Power bank
DDR3
Secondary power
Primary power
!!!
SYS
UART no STD!
SPI_CS1_N
Interface unit
M.2 connector
I2C/UART no STD!
Ethernet
SPI_CS0_N
SPI_CLK
USB3
OLED
SPI Flash
mPCIe connector

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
